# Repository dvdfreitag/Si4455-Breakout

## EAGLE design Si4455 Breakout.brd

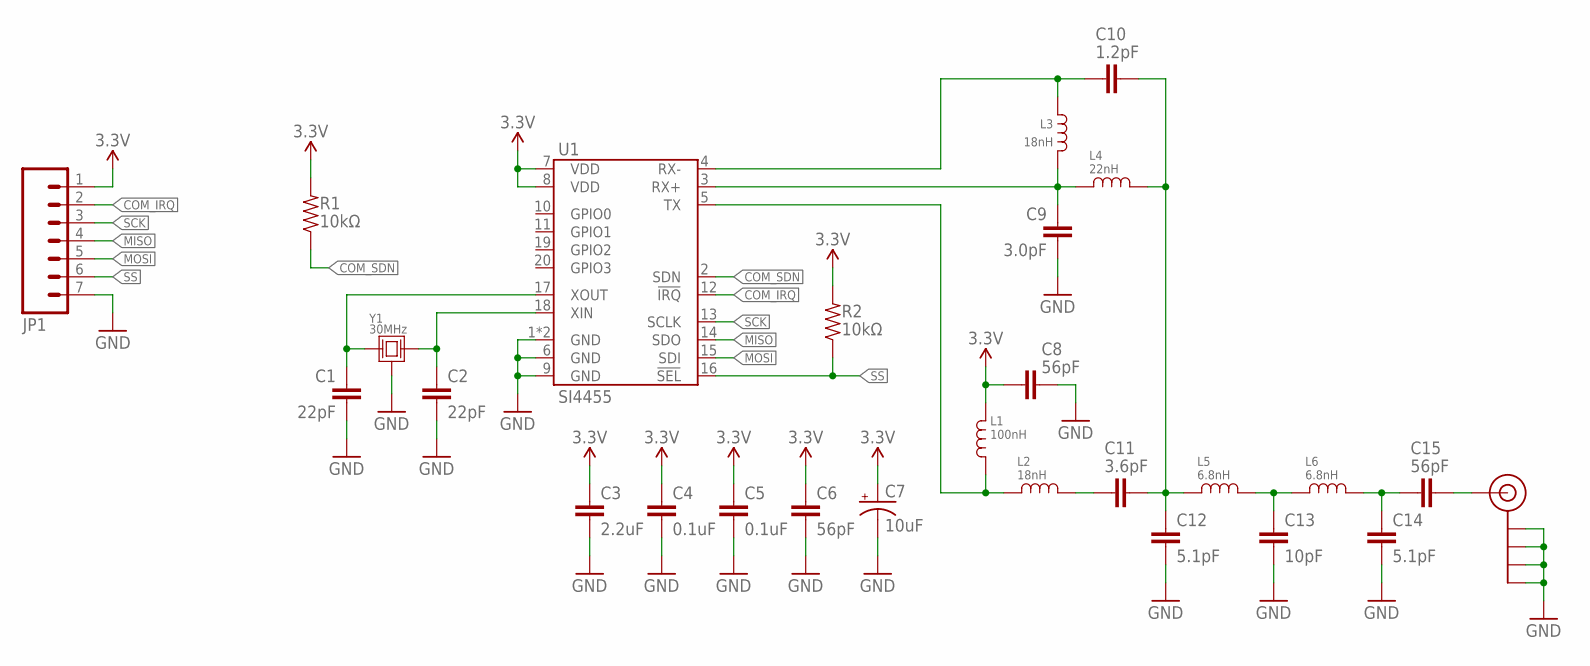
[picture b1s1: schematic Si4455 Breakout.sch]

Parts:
C1, C2: 22pF; 0402-CAP
C3: 2.2uF; 0402-CAP
C4, C5: 0.1uF; 0402-CAP
C6, C8, C15: 56pF; 0402-CAP
C7: 10uF; 0805-CAP_POL
C9: 3.0pF; 0402-CAP
C10: 1.2pF; 0402-CAP
C11: 3.6pF; 0402-CAP
C12, C14: 5.1pF; 0402-CAP
C13: 10pF; 0402-CAP
J$1: SMA_EDGE; SMA-EDGE
JP1: M07; 1X07
L1: 100nH; 0402-INDUCTOR
L2, L3: 18nH; 0402-INDUCTOR
L4: 22nH; 0402-INDUCTOR
L5, L6: 6.8nH; 0402-INDUCTOR
R1, R2: 10kΩ; 0402-RES
U1: SI4455
Y1: 30MHz; FA-238

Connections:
3.3V: C3.1, C4.1, C5.1, C6.1, C7.A (+), C8.1, JP1.1, L1.2, R1.2, R2.2, U1.7 (VDD), U1.8 (VDD)
COM_IRQ: JP1.2, U1.12 (!IRQ)
COM_SDN: R1.1, U1.2 (SDN)
GND: C1.2, C2.2, C3.2, C4.2, C5.2, C6.2, C7.C (-), C8.2, C9.2, C12.2, C13.2, C14.2, J$1.GND@0 (GND), J$1.GND@1 (GND), J$1.GND@2 (GND), J$1.GND@3 (GND), JP1.7, U1.1 (GND), U1.6 (GND), U1.9 (GND), U1.EP (GND), Y1.2 (GND), Y1.4 (GND)
MISO: JP1.4, U1.14 (SDO)
MOSI: JP1.5, U1.15 (SDI)
unnamed: C15.2, J$1.SIG (SIGNAL)
unnamed: C14.1, C15.1, L6.2
unnamed: C13.1, L5.2, L6.1
unnamed: C11.1, L2.2
unnamed: L1.1, L2.1, U1.5 (TX)
unnamed: C10.1, L3.2, U1.4 (RX-)
unnamed: C1.1, U1.17 (XOUT), Y1.1
unnamed: C2.1, U1.18 (XIN), Y1.3 (2)
unnamed: C9.1, L3.1, L4.1, U1.3 (RX+)
unnamed: C10.2, C11.2, C12.1, L4.2, L5.1
SCK: JP1.3, U1.13 (SCLK)
SS: JP1.6, R2.1, U1.16 (!SEL)

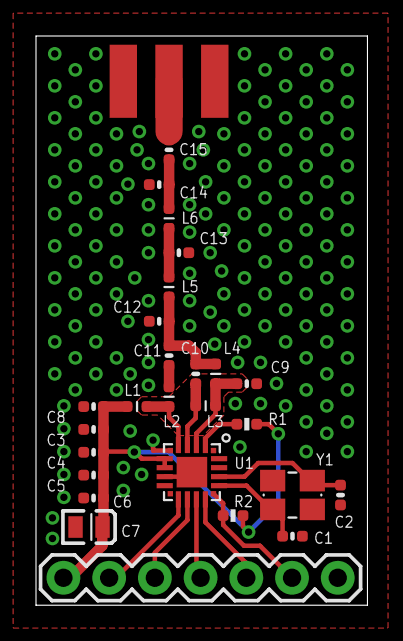
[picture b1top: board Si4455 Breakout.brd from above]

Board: 2 copper layers, 18.4 x 31.6 mm, 27 parts (0 on the bottom side), 18 nets.

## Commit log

2016-08-12 Create LICENSE

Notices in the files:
parts and their libraries:
SparkFun-Connectors: Licensing: CC v3.0 Share-Alike You are welcome to use this library for commercial purposes.
